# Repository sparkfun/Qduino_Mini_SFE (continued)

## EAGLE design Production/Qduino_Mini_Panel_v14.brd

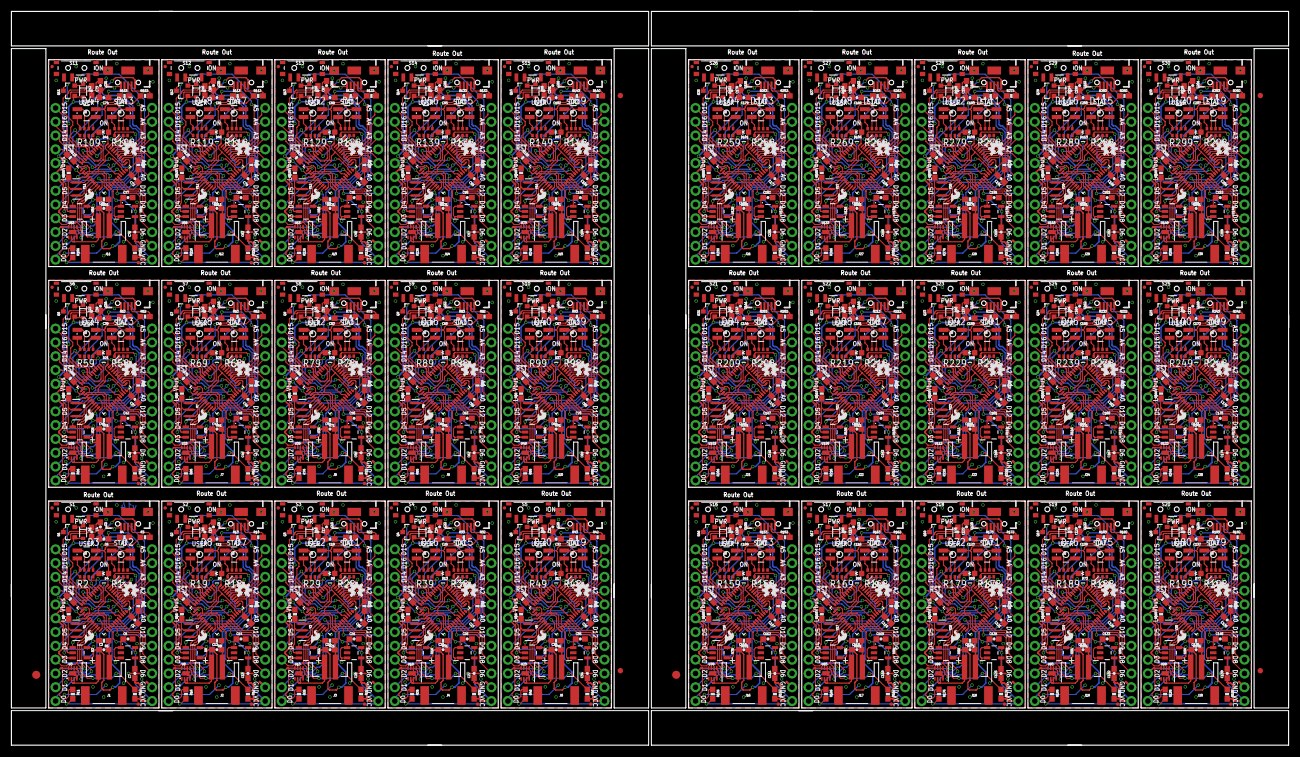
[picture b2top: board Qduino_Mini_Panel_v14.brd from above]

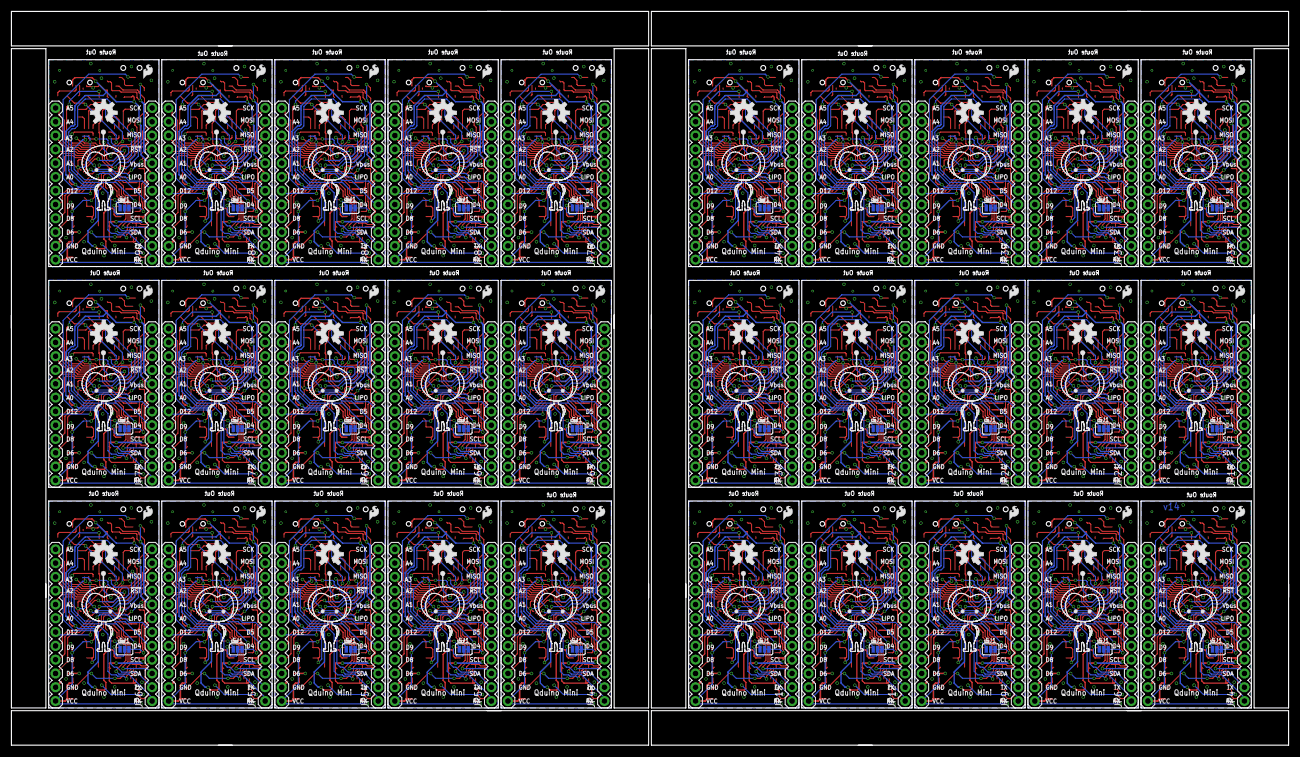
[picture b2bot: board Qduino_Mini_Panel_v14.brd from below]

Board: 2 copper layers, 235.2 x 135.1 mm, 1206 parts (180 on the bottom side), 1530 nets.

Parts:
C1, C2, C8, C9, C15, C16, C22, C23, C29, C30, C36, C37, C43, C44, C50, C51, C57, C58, C64, C65, C71, C72, C78, C79, C85, C86, C92, C93, C99, C100, C106, C107, C113, C114, C120, C121, C127, C128, C134, C135, C141, C142, C148, C149, C155, C156, C162, C163, C169, C170, C176, C177, C183, C184, C190, C191, C197, C198, C204, C205: 4.7uF; 0603-CAP
C3, C4, C5, C10, C12, C14, C17, C19, C21, C24, C26, C28, C31, C33, C35, C38, C40, C42, C45, C47, C49, C52, C54, C56, C59, C61, C63, C66, C68, C70, C73, C75, C77, C80, C82, C84, C87, C89, C91, C94, C96, C98, C101, C103, C105, C108, C110, C112, C115, C117, C119, C122, C124, C126, C129, C131, C133, C136, C138, C140, C143, C145, C147, C150, C152, C154, C157, C159, C161, C164, C166, C168, C171, C173, C175, C178, C180, C182, C185, C187, C189, C192, C194, C196, C199, C201, C203, C206, C208, C210: 1uF; 0603-CAP
C6, C11, C18, C25, C32, C39, C46, C53, C60, C67, C74, C81, C88, C95, C102, C109, C116, C123, C130, C137, C144, C151, C158, C165, C172, C179, C186, C193, C200, C207: 0.1uF; 0603-CAP
C7, C13, C20, C27, C34, C41, C48, C55, C62, C69, C76, C83, C90, C97, C104, C111, C118, C125, C132, C139, C146, C153, C160, C167, C174, C181, C188, C195, C202, C209: 2.2uF; 0603-CAP
D1, D6, D10, D14, D18, D22, D26, D30, D34, D38, D42, D46, D50, D54, D58, D62, D66, D70, D74, D78, D82, D86, D90, D94, D98, D102, D106, D110, D114, D118: BAT20J; SOD-323
D2, D3, D7, D8, D11, D12, D15, D16, D19, D20, D23, D24, D27, D28, D31, D32, D35, D36, D39, D40, D43, D44, D47, D48, D51, D52, D55, D56, D59, D60, D63, D64, D67, D68, D71, D72, D75, D76, D79, D80, D83, D84, D87, D88, D91, D92, D95, D96, D99, D100, D103, D104, D107, D108, D111, D112, D115, D116, D119, D120: P-LCC-4-3
D4, D5, D9, D13, D17, D21, D25, D29, D33, D37, D41, D45, D49, D53, D57, D61, D65, D69, D73, D77, D81, D85, D89, D93, D97, D101, D105, D109, D113, D117: GREEN; LED-0603
E$1, E$4: FIDUCIAL-1.5X3
E$2, E$3, E$5, E$6: FIDUCIAL-1X2
FID1, FID2, FID3, FID4, FID5, FID6, FID7, FID8, FID9, FID10, FID11, FID12, FID13, FID14, FID15, FID16, FID17, FID18, FID19, FID20, FID21, FID22, FID23, FID24, FID25, FID26, FID27, FID28, FID29, FID30, FID31, FID32, FID33, FID34, FID35, FID36, FID37, FID38, FID39, FID40, FID41, FID42, FID43, FID44, FID45, FID46, FID47, FID48, FID49, FID50, FID51, FID52, FID53, FID54, FID55, FID56, FID57, FID58, FID59, FID60: FIDUCIALUFIDUCIAL; MICRO-FIDUCIAL
J1, J2, J3, J4, J5, J6, J7, J8, J9, J10, J11, J12, J13, J14, J15, J16, J17, J18, J19, J20, J21, J22, J23, J24, J25, J26, J27, J28, J29, J30: LiPo; JST-2-SMD
JP1, JP2, JP7, JP10, JP13, JP16, JP19, JP22, JP25, JP28, JP31, JP34, JP37, JP40, JP43, JP46, JP49, JP52, JP55, JP58, JP61, JP64, JP67, JP70, JP73, JP76, JP79, JP82, JP85, JP88: USB-B-MICRO-SMD_V03
JP3, JP4, JP5, JP6, JP8, JP9, JP11, JP12, JP14, JP15, JP17, JP18, JP20, JP21, JP23, JP24, JP26, JP27, JP29, JP30, JP32, JP33, JP35, JP36, JP38, JP39, JP41, JP42, JP44, JP45, JP47, JP48, JP50, JP51, JP53, JP54, JP56, JP57, JP59, JP60, JP62, JP63, JP65, JP66, JP68, JP69, JP71, JP72, JP74, JP75, JP77, JP78, JP80, JP81, JP83, JP84, JP86, JP87, JP89, JP90: 1X12
LOGO1, LOGO4, LOGO7, LOGO10, LOGO13, LOGO16, LOGO19, LOGO22, LOGO25, LOGO28, LOGO31, LOGO34, LOGO37, LOGO40, LOGO43, LOGO46, LOGO49, LOGO52, LOGO55, LOGO58, LOGO61, LOGO64, LOGO67, LOGO70, LOGO73, LOGO76, LOGO79, LOGO82, LOGO85, LOGO88: OSHW-LOGOS; OSHW-LOGO-S
LOGO2, LOGO5, LOGO8, LOGO11, LOGO14, LOGO17, LOGO20, LOGO23, LOGO26, LOGO29, LOGO32, LOGO35, LOGO38, LOGO41, LOGO44, LOGO47, LOGO50, LOGO53, LOGO56, LOGO59, LOGO62, LOGO65, LOGO68, LOGO71, LOGO74, LOGO77, LOGO80, LOGO83, LOGO86, LOGO89: SFE_LOGO_FLAME.1_INCH; SFE_LOGO_FLAME_.1
LOGO3, LOGO6, LOGO9, LOGO12, LOGO15, LOGO18, LOGO21, LOGO24, LOGO27, LOGO30, LOGO33, LOGO36, LOGO39, LOGO42, LOGO45, LOGO48, LOGO51, LOGO54, LOGO57, LOGO60, LOGO63, LOGO66, LOGO69, LOGO72, LOGO75, LOGO78, LOGO81, LOGO84, LOGO87, LOGO90: SFE_LOGO_FLAME.1_INCH; SFE_LOGO_FLAME_.1@1
Q1, Q2, Q3, Q4, Q5, Q6, Q7, Q8, Q9, Q10, Q11, Q12, Q13, Q14, Q15, Q16, Q17, Q18, Q19, Q20, Q21, Q22, Q23, Q24, Q25, Q26, Q27, Q28, Q29, Q30: ZXMP6A13FTA; SOT23-3
R1, R2, R18, R19, R28, R29, R38, R39, R48, R49, R58, R59, R68, R69, R78, R79, R88, R89, R98, R99, R108, R109, R118, R119, R128, R129, R138, R139, R148, R149, R158, R159, R168, R169, R178, R179, R188, R189, R198, R199, R208, R209, R218, R219, R228, R229, R238, R239, R248, R249, R258, R259, R268, R269, R278, R279, R288, R289, R298, R299: 1KΩ; 0603-ARV
R3, R4, R10, R13, R22, R23, R32, R33, R42, R43, R52, R53, R62, R63, R72, R73, R82, R83, R92, R93, R102, R103, R112, R113, R122, R123, R132, R133, R142, R143, R152, R153, R162, R163, R172, R173, R182, R183, R192, R193, R202, R203, R212, R213, R222, R223, R232, R233, R242, R243, R252, R253, R262, R263, R272, R273, R282, R283, R292, R293: 22; 0603-RES
R5, R9, R21, R31, R41, R51, R61, R71, R81, R91, R101, R111, R121, R131, R141, R151, R161, R171, R181, R191, R201, R211, R221, R231, R241, R251, R261, R271, R281, R291: 2.0k; 0603-RES
R6, R14, R24, R34, R44, R54, R64, R74, R84, R94, R104, R114, R124, R134, R144, R154, R164, R174, R184, R194, R204, R214, R224, R234, R244, R254, R264, R274, R284, R294: 100k; 0603-RES
R7, R8, R15, R20, R25, R30, R35, R40, R45, R50, R55, R60, R65, R70, R75, R80, R85, R90, R95, R100, R105, R110, R115, R120, R125, R130, R135, R140, R145, R150, R155, R160, R165, R170, R175, R180, R185, R190, R195, R200, R205, R210, R215, R220, R225, R230, R235, R240, R245, R250, R255, R260, R265, R270, R275, R280, R285, R290, R295, R300: 10K; 0603-RES
R11, R12, R16, R17, R26, R27, R36, R37, R46, R47, R56, R57, R66, R67, R76, R77, R86, R87, R96, R97, R106, R107, R116, R117, R126, R127, R136, R137, R146, R147, R156, R157, R166, R167, R176, R177, R186, R187, R196, R197, R206, R207, R216, R217, R226, R227, R236, R237, R246, R247, R256, R257, R266, R267, R276, R277, R286, R287, R296, R297: 4.7K; 0603-RES
S1, S2, S3, S4, S5, S6, S7, S8, S9, S10, S11, S12, S13, S14, S15, S16, S17, S18, S19, S20, S21, S22, S23, S24, S25, S26, S27, S28, S29, S30: POWER; SWITCH-SPST-SMD-A
SJ1, SJ2, SJ3, SJ4, SJ5, SJ6, SJ7, SJ8, SJ9, SJ10, SJ11, SJ12, SJ13, SJ14, SJ15, SJ16, SJ17, SJ18, SJ19, SJ20, SJ21, SJ22, SJ23, SJ24, SJ25, SJ26, SJ27, SJ28, SJ29, SJ30: PAD-JUMPER-3-2OF3_NC_BY_TRACE_YES_SILK_FULL_BOX
U1, U7, U12, U17, U22, U27, U32, U37, U42, U47, U52, U57, U62, U67, U72, U77, U82, U87, U92, U97, U102, U107, U112, U117, U122, U127, U132, U137, U142, U147: ATMEGA32U41:1-LESS_PASTE; QFN-44-NOPAD_1:1-LESS_PASTE
U2, U6, U11, U16, U21, U26, U31, U36, U41, U46, U51, U56, U61, U66, U71, U76, U81, U86, U91, U96, U101, U106, U111, U116, U121, U126, U131, U136, U141, U146: MCP73831; SOT23-5
U3, U8, U13, U18, U23, U28, U33, U38, U43, U48, U53, U58, U63, U68, U73, U78, U83, U88, U93, U98, U103, U108, U113, U118, U123, U128, U133, U138, U143, U148: MAX17048; DFN-8
U4, U9, U14, U19, U24, U29, U34, U39, U44, U49, U54, U59, U64, U69, U74, U79, U84, U89, U94, U99, U104, U109, U114, U119, U124, U129, U134, U139, U144, U149: AP2112K-3.3TRG-1; SOT23-5
U5, U10, U15, U20, U25, U30, U35, U40, U45, U50, U55, U60, U65, U70, U75, U80, U85, U90, U95, U100, U105, U110, U115, U120, U125, U130, U135, U140, U145, U150: MIGHTYQ-L-SILK; LOGO-LARGE-SILK
U$1, U$2, U$3, U$4, U$5, U$6, U$7, U$8, U$9, U$10, U$11, U$12, U$13, U$14, U$15, U$16, U$17, U$18, U$19, U$20, U$21, U$22, U$23, U$24, U$25, U$26, U$27, U$28, U$29, U$30: OSHW-LOGO-M@1
Y1, Y2, Y3, Y4, Y5, Y6, Y7, Y8, Y9, Y10, Y11, Y12, Y13, Y14, Y15, Y16, Y17, Y18, Y19, Y20, Y21, Y22, Y23, Y24, Y25, Y26, Y27, Y28, Y29, Y30: 8MHZ; RESONATOR-SMD

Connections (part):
!ALRT: U1.1, U3.P$5
!ALRT1: U7.1, U8.P$5
!ALRT2: U12.1, U13.P$5
!ALRT3: U17.1, U18.P$5
!ALRT4: U22.1, U23.P$5
!ALRT5: U27.1, U28.P$5
!ALRT6: U32.1, U33.P$5
!ALRT7: U37.1, U38.P$5
!ALRT8: U42.1, U43.P$5
!ALRT9: U47.1, U48.P$5
!ALRT10: U52.1, U53.P$5
!ALRT11: U57.1, U58.P$5
!ALRT12: U62.1, U63.P$5
!ALRT13: U67.1, U68.P$5
!ALRT14: U72.1, U73.P$5
!ALRT15: U77.1, U78.P$5
!ALRT16: U82.1, U83.P$5
!ALRT17: U87.1, U88.P$5
!ALRT18: U92.1, U93.P$5
!ALRT19: U97.1, U98.P$5
!ALRT20: U102.1, U103.P$5
!ALRT21: U107.1, U108.P$5
!ALRT22: U112.1, U113.P$5
!ALRT23: U117.1, U118.P$5
!ALRT24: U122.1, U123.P$5
!ALRT25: U127.1, U128.P$5
!ALRT26: U132.1, U133.P$5
!ALRT27: U137.1, U138.P$5
!ALRT28: U142.1, U143.P$5
!ALRT29: U147.1, U148.P$5
!RST: JP4.9, R8.1, U1.13
!RST1: JP6.9, R20.1, U7.13
!RST2: JP9.9, R30.1, U12.13
!RST3: JP12.9, R40.1, U17.13
!RST4: JP15.9, R50.1, U22.13
!RST5: JP18.9, R60.1, U27.13
!RST6: JP21.9, R70.1, U32.13
!RST7: JP24.9, R80.1, U37.13
!RST8: JP27.9, R90.1, U42.13
!RST9: JP30.9, R100.1, U47.13
!RST10: JP33.9, R110.1, U52.13
!RST11: JP36.9, R120.1, U57.13
!RST12: JP39.9, R130.1, U62.13
!RST13: JP42.9, R140.1, U67.13
!RST14: JP45.9, R150.1, U72.13
!RST15: JP48.9, R160.1, U77.13
!RST16: JP51.9, R170.1, U82.13
!RST17: JP54.9, R180.1, U87.13
!RST18: JP57.9, R190.1, U92.13
!RST19: JP60.9, R200.1, U97.13
!RST20: JP63.9, R210.1, U102.13
!RST21: JP66.9, R220.1, U107.13
!RST22: JP69.9, R230.1, U112.13
!RST23: JP72.9, R240.1, U117.13
!RST24: JP75.9, R250.1, U122.13
!RST25: JP78.9, R260.1, U127.13
!RST26: JP81.9, R270.1, U132.13
!RST27: JP84.9, R280.1, U137.13
!RST28: JP87.9, R290.1, U142.13
!RST29: JP90.9, R300.1, U147.13
A0: JP3.7, U1.36
A1: JP3.8, U1.37
A2: JP3.9, U1.38
A3: JP3.10, U1.39
A4: JP3.11, U1.40
A5: JP3.12, U1.41
A6: JP5.7, U7.36
A7: JP5.8, U7.37
A8: JP5.9, U7.38
A9: JP5.10, U7.39
A10: JP5.11, U7.40
A11: JP5.12, U7.41
A12: JP8.7, U12.36
A13: JP8.8, U12.37
A14: JP8.9, U12.38
A15: JP8.10, U12.39
A16: JP8.11, U12.40
A17: JP8.12, U12.41
A18: JP11.7, U17.36
A19: JP11.8, U17.37
A20: JP11.9, U17.38
A21: JP11.10, U17.39
A22: JP11.11, U17.40
A23: JP11.12, U17.41
A24: JP14.7, U22.36
A25: JP14.8, U22.37
A26: JP14.9, U22.38
A27: JP14.10, U22.39
A28: JP14.11, U22.40
A29: JP14.12, U22.41
A30: JP17.7, U27.36
A31: JP17.8, U27.37
A32: JP17.9, U27.38
A33: JP17.10, U27.39
A34: JP17.11, U27.40
A35: JP17.12, U27.41
A36: JP20.7, U32.36
A37: JP20.8, U32.37
A38: JP20.9, U32.38
A39: JP20.10, U32.39
A40: JP20.11, U32.40
A41: JP20.12, U32.41
A42: JP23.7, U37.36
A43: JP23.8, U37.37
A44: JP23.9, U37.38
A45: JP23.10, U37.39
A46: JP23.11, U37.40
A47: JP23.12, U37.41
A48: JP26.7, U42.36
A49: JP26.8, U42.37
A50: JP26.9, U42.38
A51: JP26.10, U42.39
A52: JP26.11, U42.40
A53: JP26.12, U42.41
A54: JP29.7, U47.36
A55: JP29.8, U47.37
A56: JP29.9, U47.38
A57: JP29.10, U47.39
A58: JP29.11, U47.40
A59: JP29.12, U47.41
A60: JP32.7, U52.36
A61: JP32.8, U52.37
A62: JP32.9, U52.38
A63: JP32.10, U52.39
A64: JP32.11, U52.40
A65: JP32.12, U52.41
A66: JP35.7, U57.36
A67: JP35.8, U57.37
A68: JP35.9, U57.38
A69: JP35.10, U57.39
A70: JP35.11, U57.40
A71: JP35.12, U57.41
A72: JP38.7, U62.36
A73: JP38.8, U62.37
A74: JP38.9, U62.38
A75: JP38.10, U62.39
A76: JP38.11, U62.40
A77: JP38.12, U62.41
A78: JP41.7, U67.36
A79: JP41.8, U67.37
A80: JP41.9, U67.38
A81: JP41.10, U67.39
A82: JP41.11, U67.40
A83: JP41.12, U67.41
A84: JP44.7, U72.36
A85: JP44.8, U72.37
A86: JP44.9, U72.38
A87: JP44.10, U72.39
A88: JP44.11, U72.40
A89: JP44.12, U72.41
A90: JP47.7, U77.36
A91: JP47.8, U77.37
A92: JP47.9, U77.38
A93: JP47.10, U77.39
A94: JP47.11, U77.40
A95: JP47.12, U77.41
A96: JP50.7, U82.36
A97: JP50.8, U82.37
A98: JP50.9, U82.38
A99: JP50.10, U82.39
A100: JP50.11, U82.40
A101: JP50.12, U82.41
A102: JP53.7, U87.36
A103: JP53.8, U87.37
A104: JP53.9, U87.38
A105: JP53.10, U87.39
A106: JP53.11, U87.40
A107: JP53.12, U87.41
A108: JP56.7, U92.36
A109: JP56.8, U92.37
A110: JP56.9, U92.38
A111: JP56.10, U92.39
A112: JP56.11, U92.40
A113: JP56.12, U92.41
A114: JP59.7, U97.36
A115: JP59.8, U97.37
A116: JP59.9, U97.38
A117: JP59.10, U97.39
A118: JP59.11, U97.40
A119: JP59.12, U97.41
A120: JP62.7, U102.36
A121: JP62.8, U102.37
A122: JP62.9, U102.38
A123: JP62.10, U102.39
A124: JP62.11, U102.40
A125: JP62.12, U102.41
A126: JP65.7, U107.36
A127: JP65.8, U107.37
A128: JP65.9, U107.38
A129: JP65.10, U107.39
A130: JP65.11, U107.40
A131: JP65.12, U107.41
A132: JP68.7, U112.36
A133: JP68.8, U112.37
A134: JP68.9, U112.38
A135: JP68.10, U112.39
A136: JP68.11, U112.40
A137: JP68.12, U112.41
A138: JP71.7, U117.36
A139: JP71.8, U117.37
A140: JP71.9, U117.38
A141: JP71.10, U117.39
A142: JP71.11, U117.40
A143: JP71.12, U117.41
A144: JP74.7, U122.36
A145: JP74.8, U122.37
A146: JP74.9, U122.38
A147: JP74.10, U122.39
A148: JP74.11, U122.40
A149: JP74.12, U122.41
A150: JP77.7, U127.36
A151: JP77.8, U127.37
A152: JP77.9, U127.38
A153: JP77.10, U127.39
A154: JP77.11, U127.40
A155: JP77.12, U127.41
A156: JP80.7, U132.36
A157: JP80.8, U132.37
A158: JP80.9, U132.38
A159: JP80.10, U132.39
A160: JP80.11, U132.40
A161: JP80.12, U132.41
A162: JP83.7, U137.36
A163: JP83.8, U137.37
A164: JP83.9, U137.38
A165: JP83.10, U137.39
A166: JP83.11, U137.40
A167: JP83.12, U137.41
A168: JP86.7, U142.36
A169: JP86.8, U142.37
A170: JP86.9, U142.38
A171: JP86.10, U142.39
A172: JP86.11, U142.40
A173: JP86.12, U142.41
A174: JP89.7, U147.36
A175: JP89.8, U147.37
A176: JP89.9, U147.38
A177: JP89.10, U147.39
A178: JP89.11, U147.40
A179: JP89.12, U147.41
AREF: C6.1, U1.42
AREF1: C11.1, U7.42
AREF2: C18.1, U12.42
AREF3: C25.1, U17.42
AREF4: C32.1, U22.42
AREF5: C39.1, U27.42
AREF6: C46.1, U32.42
AREF7: C53.1, U37.42
AREF8: C60.1, U42.42
AREF9: C67.1, U47.42
AREF10: C74.1, U52.42
AREF11: C81.1, U57.42
AREF12: C88.1, U62.42
AREF13: C95.1, U67.42
AREF14: C102.1, U72.42
AREF15: C109.1, U77.42
AREF16: C116.1, U82.42
AREF17: C123.1, U87.42
AREF18: C130.1, U92.42
AREF19: C137.1, U97.42
AREF20: C144.1, U102.42
AREF21: C151.1, U107.42
AREF22: C158.1, U112.42
AREF23: C165.1, U117.42
AREF24: C172.1, U122.42
AREF25: C179.1, U127.42
AREF26: C186.1, U132.42
AREF27: C193.1, U137.42
AREF28: C200.1, U142.42
AREF29: C207.1, U147.42
D1: JP6.5, U7.25
D2: JP6.6, U7.31
D3: JP5.4, U7.28
D4: JP4.5, U1.25
D5: JP4.6, U1.31
D6: JP3.3, U1.27
D7: JP5.5, U7.29
D8: JP3.4, U1.28
D9: JP3.5, U1.29
D10: R2.2, U1.30
D11: R2.1, U1.12
D12: JP3.6, U1.26
D13: R2.3, U1.32
D14: R19.2, U7.30
D15: R19.1, U7.12
D16: JP5.6, U7.26
D17: R19.3, U7.32
D18: JP5.3, U7.27
D19: JP9.5, U12.25
D20: JP9.6, U12.31
D21: JP8.4, U12.28
D22: JP8.5, U12.29
D23: R29.2, U12.30
D24: R29.1, U12.12
D25: JP8.6, U12.26
D26: R29.3, U12.32
D27: JP8.3, U12.27
D28: JP12.5, U17.25
D29: JP12.6, U17.31
D30: JP11.4, U17.28
D31: JP11.5, U17.29
D32: R39.2, U17.30
D33: R39.1, U17.12
D34: JP11.6, U17.26
D35: R39.3, U17.32
D36: JP11.3, U17.27
D37: JP15.5, U22.25
D38: JP15.6, U22.31
D39: JP14.4, U22.28
D40: JP14.5, U22.29
D41: R49.2, U22.30
D42: R49.1, U22.12
D43: JP14.6, U22.26
D44: R49.3, U22.32
D45: JP14.3, U22.27
D46: JP18.5, U27.25
D47: JP18.6, U27.31
D48: JP17.4, U27.28
D49: JP17.5, U27.29
D50: R59.2, U27.30
D51: R59.1, U27.12
D52: JP17.6, U27.26
D53: R59.3, U27.32
D54: JP17.3, U27.27
D55: JP21.5, U32.25
D56: JP21.6, U32.31
D57: JP20.4, U32.28
D58: JP20.5, U32.29
D59: R69.2, U32.30
D60: R69.1, U32.12
D61: JP20.6, U32.26
D62: R69.3, U32.32
D63: JP20.3, U32.27
D64: JP24.5, U37.25
D65: JP24.6, U37.31
D66: JP23.4, U37.28
D67: JP23.5, U37.29
D68: R79.2, U37.30
D69: R79.1, U37.12
D70: JP23.6, U37.26
D71: R79.3, U37.32
D72: JP23.3, U37.27
D73: JP27.5, U42.25
D74: JP27.6, U42.31
D75: JP26.4, U42.28
D76: JP26.5, U42.29
D77: R89.2, U42.30
D78: R89.1, U42.12
D79: JP26.6, U42.26
D80: R89.3, U42.32
D81: JP26.3, U42.27
D82: JP30.5, U47.25
D83: JP30.6, U47.31
D84: JP29.4, U47.28
D85: JP29.5, U47.29
D86: R99.2, U47.30
D87: R99.1, U47.12
D88: JP29.6, U47.26
D89: R99.3, U47.32
D90: JP29.3, U47.27
D91: JP33.5, U52.25
D92: JP33.6, U52.31
D93: JP32.4, U52.28
D94: JP32.5, U52.29
D95: R109.2, U52.30
D96: R109.1, U52.12
D97: JP32.6, U52.26
D98: R109.3, U52.32
D99: JP32.3, U52.27
D100: JP36.5, U57.25
D101: JP36.6, U57.31
D102: JP35.4, U57.28
D103: JP35.5, U57.29
D104: R119.2, U57.30
D105: R119.1, U57.12
D106: JP35.6, U57.26
D107: R119.3, U57.32
D108: JP35.3, U57.27
D109: JP39.5, U62.25
D110: JP39.6, U62.31
D111: JP38.4, U62.28
D112: JP38.5, U62.29
D113: R129.2, U62.30
D114: R129.1, U62.12
D115: JP38.6, U62.26
D116: R129.3, U62.32
D117: JP38.3, U62.27
D118: JP42.5, U67.25
D119: JP42.6, U67.31
D120: JP41.4, U67.28
D121: JP41.5, U67.29
D122: R139.2, U67.30
D123: R139.1, U67.12
D124: JP41.6, U67.26
D125: R139.3, U67.32
D126: JP41.3, U67.27
D127: JP45.5, U72.25
D128: JP45.6, U72.31
D129: JP44.4, U72.28
D130: JP44.5, U72.29
D131: R149.2, U72.30
D132: R149.1, U72.12
D133: JP44.6, U72.26
D134: R149.3, U72.32
D135: JP44.3, U72.27
D136: JP48.5, U77.25
D137: JP48.6, U77.31
D138: JP47.4, U77.28
D139: JP47.5, U77.29
D140: R159.2, U77.30
D141: R159.1, U77.12
D142: JP47.6, U77.26
D143: R159.3, U77.32
D144: JP47.3, U77.27
D145: JP51.5, U82.25
D146: JP51.6, U82.31
D147: JP50.4, U82.28
D148: JP50.5, U82.29
D149: R169.2, U82.30
D150: R169.1, U82.12
D151: JP50.6, U82.26
D152: R169.3, U82.32
D153: JP50.3, U82.27
D154: JP54.5, U87.25
D155: JP54.6, U87.31
D156: JP53.4, U87.28
D157: JP53.5, U87.29
D158: R179.2, U87.30
D159: R179.1, U87.12
D160: JP53.6, U87.26
D161: R179.3, U87.32
D162: JP53.3, U87.27
D163: JP57.5, U92.25
D164: JP57.6, U92.31
D165: JP56.4, U92.28
D166: JP56.5, U92.29
D167: R189.2, U92.30
D168: R189.1, U92.12
D169: JP56.6, U92.26
D170: R189.3, U92.32
D171: JP56.3, U92.27
D172: JP60.5, U97.25
D173: JP60.6, U97.31
D174: JP59.4, U97.28
D175: JP59.5, U97.29
D176: R199.2, U97.30
D177: R199.1, U97.12
D178: JP59.6, U97.26
D179: R199.3, U97.32
D180: JP59.3, U97.27
D181: JP63.5, U102.25
D182: JP63.6, U102.31
D183: JP62.4, U102.28
D184: JP62.5, U102.29
D185: R209.2, U102.30
D186: R209.1, U102.12
D187: JP62.6, U102.26
D188: R209.3, U102.32
D189: JP62.3, U102.27
D190: JP66.5, U107.25
D191: JP66.6, U107.31
D192: JP65.4, U107.28
D193: JP65.5, U107.29
D194: R219.2, U107.30
D195: R219.1, U107.12
D196: JP65.6, U107.26
D197: R219.3, U107.32
D198: JP65.3, U107.27
D199: JP69.5, U112.25
D200: JP69.6, U112.31
D201: JP68.4, U112.28
D202: JP68.5, U112.29
D203: R229.2, U112.30
D204: R229.1, U112.12
D205: JP68.6, U112.26
D206: R229.3, U112.32
D207: JP68.3, U112.27
D208: JP72.5, U117.25
D209: JP72.6, U117.31
D210: JP71.4, U117.28
D211: JP71.5, U117.29
D212: R239.2, U117.30
D213: R239.1, U117.12
D214: JP71.6, U117.26
D215: R239.3, U117.32
D216: JP71.3, U117.27
D217: JP75.5, U122.25
D218: JP75.6, U122.31
D219: JP74.4, U122.28
D220: JP74.5, U122.29
D221: R249.2, U122.30
D222: R249.1, U122.12
D223: JP74.6, U122.26
D224: R249.3, U122.32
D225: JP74.3, U122.27
D226: JP78.5, U127.25
D227: JP78.6, U127.31
D228: JP77.4, U127.28
D229: JP77.5, U127.29
D230: R259.2, U127.30
D231: R259.1, U127.12
D232: JP77.6, U127.26
D233: R259.3, U127.32
D234: JP77.3, U127.27
D235: JP81.5, U132.25
D236: JP81.6, U132.31
D237: JP80.4, U132.28
D238: JP80.5, U132.29
D239: R269.2, U132.30
D240: R269.1, U132.12
D241: JP80.6, U132.26
D242: R269.3, U132.32
D243: JP80.3, U132.27
D244: JP84.5, U137.25
D245: JP84.6, U137.31
D246: JP83.4, U137.28
D247: JP83.5, U137.29
D248: R279.2, U137.30
D249: R279.1, U137.12
D250: JP83.6, U137.26
D251: R279.3, U137.32
D252: JP83.3, U137.27
D253: JP87.5, U142.25
D254: JP87.6, U142.31
D255: JP86.4, U142.28
D256: JP86.5, U142.29
D257: R289.2, U142.30
D258: R289.1, U142.12
D259: JP86.6, U142.26
D260: R289.3, U142.32
D261: JP86.3, U142.27
D262: JP90.5, U147.25
D263: JP90.6, U147.31
D264: JP89.4, U147.28
D265: JP89.5, U147.29
D266: R299.2, U147.30
D267: R299.1, U147.12
D268: JP89.6, U147.26
D269: R299.3, U147.32
D270: JP89.3, U147.27
D+: R4.1, U1.4
D+1: R13.1, U7.4
D+2: R23.1, U12.4
D+3: R33.1, U17.4
D+4: R43.1, U22.4
D+5: R53.1, U27.4
D+6: R63.1, U32.4
D+7: R73.1, U37.4
D+8: R83.1, U42.4
D+9: R93.1, U47.4
D+10: R103.1, U52.4
D+11: R113.1, U57.4
D+12: R123.1, U62.4
D+13: R133.1, U67.4
D+14: R143.1, U72.4
D+15: R153.1, U77.4
D+16: R163.1, U82.4
D+17: R173.1, U87.4
D+18: R183.1, U92.4
D+19: R193.1, U97.4
D+20: R203.1, U102.4
D+21: R213.1, U107.4
D+22: R223.1, U112.4
D+23: R233.1, U117.4
D+24: R243.1, U122.4
D+25: R253.1, U127.4
D+26: R263.1, U132.4
D+27: R273.1, U137.4
D+28: R283.1, U142.4
D+29: R293.1, U147.4
D-: R3.1, U1.3
D-1: R10.1, U7.3
D-2: R22.1, U12.3
D-3: R32.1, U17.3
D-4: R42.1, U22.3
D-5: R52.1, U27.3
D-6: R62.1, U32.3
D-7: R72.1, U37.3
D-8: R82.1, U42.3
D-9: R92.1, U47.3
D-10: R102.1, U52.3
D-11: R112.1, U57.3
D-12: R122.1, U62.3
D-13: R132.1, U67.3
D-14: R142.1, U72.3
D-15: R152.1, U77.3
D-16: R162.1, U82.3
D-17: R172.1, U87.3
D-18: R182.1, U92.3
D-19: R192.1, U97.3
D-20: R202.1, U102.3
D-21: R212.1, U107.3
D-22: R222.1, U112.3
D-23: R232.1, U117.3
D-24: R242.1, U122.3
D-25: R252.1, U127.3
D-26: R262.1, U132.3
D-27: R272.1, U137.3
D-28: R282.1, U142.3
D-29: R292.1, U147.3
GND: C1.2, C2.2, C3.2, C4.2, C5.2, C6.2, C7.2, J1.1, JP2.GND1, JP3.2, R2.5, R5.1, R6.1, R7.1, U1.5, U1.15, U1.23, U1.33, U1.35, U1.43, U2.2, U3.P$1, U3.P$4, U3.P$6, U3.P$9, U4.2, U4.4, Y1.2
GND1: C8.2, C9.2, C10.2, C11.2, C12.2, C13.2, C14.2, J2.1, JP1.GND1, JP5.2, R9.1, R14.1, R15.1, R19.5, U6.2, U7.5, U7.15, U7.23, U7.33, U7.35, U7.43, U8.P$1, U8.P$4, U8.P$6, U8.P$9, U9.2, U9.4, Y2.2
GND2: C15.2, C16.2, C17.2, C18.2, C19.2, C20.2, C21.2, J3.1, JP7.GND1, JP8.2, R21.1, R24.1, R25.1, R29.5, U11.2, U12.5, U12.15, U12.23, U12.33, U12.35, U12.43, U13.P$1, U13.P$4, U13.P$6, U13.P$9, U14.2, U14.4, Y3.2
GND3: C22.2, C23.2, C24.2, C25.2, C26.2, C27.2, C28.2, J4.1, JP10.GND1, JP11.2, R31.1, R34.1, R35.1, R39.5, U16.2, U17.5, U17.15, U17.23, U17.33, U17.35, U17.43, U18.P$1, U18.P$4, U18.P$6, U18.P$9, U19.2, U19.4, Y4.2
GND4: C29.2, C30.2, C31.2, C32.2, C33.2, C34.2, C35.2, J5.1, JP13.GND1, JP14.2, R41.1, R44.1, R45.1, R49.5, U21.2, U22.5, U22.15, U22.23, U22.33, U22.35, U22.43, U23.P$1, U23.P$4, U23.P$6, U23.P$9, U24.2, U24.4, Y5.2
GND5: C36.2, C37.2, C38.2, C39.2, C40.2, C41.2, C42.2, J6.1, JP16.GND1, JP17.2, R51.1, R54.1, R55.1, R59.5, U26.2, U27.5, U27.15, U27.23, U27.33, U27.35, U27.43, U28.P$1, U28.P$4, U28.P$6, U28.P$9, U29.2, U29.4, Y6.2
GND6: C43.2, C44.2, C45.2, C46.2, C47.2, C48.2, C49.2, J7.1, JP19.GND1, JP20.2, R61.1, R64.1, R65.1, R69.5, U31.2, U32.5, U32.15, U32.23, U32.33, U32.35, U32.43, U33.P$1, U33.P$4, U33.P$6, U33.P$9, U34.2, U34.4, Y7.2
GND7: C50.2, C51.2, C52.2, C53.2, C54.2, C55.2, C56.2, J8.1, JP22.GND1, JP23.2, R71.1, R74.1, R75.1, R79.5, U36.2, U37.5, U37.15, U37.23, U37.33, U37.35, U37.43, U38.P$1, U38.P$4, U38.P$6, U38.P$9, U39.2, U39.4, Y8.2
GND8: C57.2, C58.2, C59.2, C60.2, C61.2, C62.2, C63.2, J9.1, JP25.GND1, JP26.2, R81.1, R84.1, R85.1, R89.5, U41.2, U42.5, U42.15, U42.23, U42.33, U42.35, U42.43, U43.P$1, U43.P$4, U43.P$6, U43.P$9, U44.2, U44.4, Y9.2
GND9: C64.2, C65.2, C66.2, C67.2, C68.2, C69.2, C70.2, J10.1, JP28.GND1, JP29.2, R91.1, R94.1, R95.1, R99.5, U46.2, U47.5, U47.15, U47.23, U47.33, U47.35, U47.43, U48.P$1, U48.P$4, U48.P$6, U48.P$9, U49.2, U49.4, Y10.2
GND10: C71.2, C72.2, C73.2, C74.2, C75.2, C76.2, C77.2, J11.1, JP31.GND1, JP32.2, R101.1, R104.1, R105.1, R109.5, U51.2, U52.5, U52.15, U52.23, U52.33, U52.35, U52.43, U53.P$1, U53.P$4, U53.P$6, U53.P$9, U54.2, U54.4, Y11.2
GND11: C78.2, C79.2, C80.2, C81.2, C82.2, C83.2, C84.2, J12.1, JP34.GND1, JP35.2, R111.1, R114.1, R115.1, R119.5, U56.2, U57.5, U57.15, U57.23, U57.33, U57.35, U57.43, U58.P$1, U58.P$4, U58.P$6, U58.P$9, U59.2, U59.4, Y12.2
GND12: C85.2, C86.2, C87.2, C88.2, C89.2, C90.2, C91.2, J13.1, JP37.GND1, JP38.2, R121.1, R124.1, R125.1, R129.5, U61.2, U62.5, U62.15, U62.23, U62.33, U62.35, U62.43, U63.P$1, U63.P$4, U63.P$6, U63.P$9, U64.2, U64.4, Y13.2
GND13: C92.2, C93.2, C94.2, C95.2, C96.2, C97.2, C98.2, J14.1, JP40.GND1, JP41.2, R131.1, R134.1, R135.1, R139.5, U66.2, U67.5, U67.15, U67.23, U67.33, U67.35, U67.43, U68.P$1, U68.P$4, U68.P$6, U68.P$9, U69.2, U69.4, Y14.2
GND14: C99.2, C100.2, C101.2, C102.2, C103.2, C104.2, C105.2, J15.1, JP43.GND1, JP44.2, R141.1, R144.1, R145.1, R149.5, U71.2, U72.5, U72.15, U72.23, U72.33, U72.35, U72.43, U73.P$1, U73.P$4, U73.P$6, U73.P$9, U74.2, U74.4, Y15.2
GND15: C106.2, C107.2, C108.2, C109.2, C110.2, C111.2, C112.2, J16.1, JP46.GND1, JP47.2, R151.1, R154.1, R155.1, R159.5, U76.2, U77.5, U77.15, U77.23, U77.33, U77.35, U77.43, U78.P$1, U78.P$4, U78.P$6, U78.P$9, U79.2, U79.4, Y16.2
GND16: C113.2, C114.2, C115.2, C116.2, C117.2, C118.2, C119.2, J17.1, JP49.GND1, JP50.2, R161.1, R164.1, R165.1, R169.5, U81.2, U82.5, U82.15, U82.23, U82.33, U82.35, U82.43, U83.P$1, U83.P$4, U83.P$6, U83.P$9, U84.2, U84.4, Y17.2
GND17: C120.2, C121.2, C122.2, C123.2, C124.2, C125.2, C126.2, J18.1, JP52.GND1, JP53.2, R171.1, R174.1, R175.1, R179.5, U86.2, U87.5, U87.15, U87.23, U87.33, U87.35, U87.43, U88.P$1, U88.P$4, U88.P$6, U88.P$9, U89.2, U89.4, Y18.2
GND18: C127.2, C128.2, C129.2, C130.2, C131.2, C132.2, C133.2, J19.1, JP55.GND1, JP56.2, R181.1, R184.1, R185.1, R189.5, U91.2, U92.5, U92.15, U92.23, U92.33, U92.35, U92.43, U93.P$1, U93.P$4, U93.P$6, U93.P$9, U94.2, U94.4, Y19.2
GND19: C134.2, C135.2, C136.2, C137.2, C138.2, C139.2, C140.2, J20.1, JP58.GND1, JP59.2, R191.1, R194.1, R195.1, R199.5, U96.2, U97.5, U97.15, U97.23, U97.33, U97.35, U97.43, U98.P$1, U98.P$4, U98.P$6, U98.P$9, U99.2, U99.4, Y20.2
GND20: C141.2, C142.2, C143.2, C144.2, C145.2, C146.2, C147.2, J21.1, JP61.GND1, JP62.2, R201.1, R204.1, R205.1, R209.5, U101.2, U102.5, U102.15, U102.23, U102.33, U102.35, U102.43, U103.P$1, U103.P$4, U103.P$6, U103.P$9, U104.2, U104.4, Y21.2
GND21: C148.2, C149.2, C150.2, C151.2, C152.2, C153.2, C154.2, J22.1, JP64.GND1, JP65.2, R211.1, R214.1, R215.1, R219.5, U106.2, U107.5, U107.15, U107.23, U107.33, U107.35, U107.43, U108.P$1, U108.P$4, U108.P$6, U108.P$9, U109.2, U109.4, Y22.2
GND22: C155.2, C156.2, C157.2, C158.2, C159.2, C160.2, C161.2, J23.1, JP67.GND1, JP68.2, R221.1, R224.1, R225.1, R229.5, U111.2, U112.5, U112.15, U112.23, U112.33, U112.35, U112.43, U113.P$1, U113.P$4, U113.P$6, U113.P$9, U114.2, U114.4, Y23.2
GND23: C162.2, C163.2, C164.2, C165.2, C166.2, C167.2, C168.2, J24.1, JP70.GND1, JP71.2, R231.1, R234.1, R235.1, R239.5, U116.2, U117.5, U117.15, U117.23, U117.33, U117.35, U117.43, U118.P$1, U118.P$4, U118.P$6, U118.P$9, U119.2, U119.4, Y24.2
GND24: C169.2, C170.2, C171.2, C172.2, C173.2, C174.2, C175.2, J25.1, JP73.GND1, JP74.2, R241.1, R244.1, R245.1, R249.5, U121.2, U122.5, U122.15, U122.23, U122.33, U122.35, U122.43, U123.P$1, U123.P$4, U123.P$6, U123.P$9, U124.2, U124.4, Y25.2
GND25: C176.2, C177.2, C178.2, C179.2, C180.2, C181.2, C182.2, J26.1, JP76.GND1, JP77.2, R251.1, R254.1, R255.1, R259.5, U126.2, U127.5, U127.15, U127.23, U127.33, U127.35, U127.43, U128.P$1, U128.P$4, U128.P$6, U128.P$9, U129.2, U129.4, Y26.2
GND26: C183.2, C184.2, C185.2, C186.2, C187.2, C188.2, C189.2, J27.1, JP79.GND1, JP80.2, R261.1, R264.1, R265.1, R269.5, U131.2, U132.5, U132.15, U132.23, U132.33, U132.35, U132.43, U133.P$1, U133.P$4, U133.P$6, U133.P$9, U134.2, U134.4, Y27.2
GND27: C190.2, C191.2, C192.2, C193.2, C194.2, C195.2, C196.2, J28.1, JP82.GND1, JP83.2, R271.1, R274.1, R275.1, R279.5, U136.2, U137.5, U137.15, U137.23, U137.33, U137.35, U137.43, U138.P$1, U138.P$4, U138.P$6, U138.P$9, U139.2, U139.4, Y28.2
GND28: C197.2, C198.2, C199.2, C200.2, C201.2, C202.2, C203.2, J29.1, JP85.GND1, JP86.2, R281.1, R284.1, R285.1, R289.5, U141.2, U142.5, U142.15, U142.23, U142.33, U142.35, U142.43, U143.P$1, U143.P$4, U143.P$6, U143.P$9, U144.2, U144.4, Y29.2
GND29: C204.2, C205.2, C206.2, C207.2, C208.2, C209.2, C210.2, J30.1, JP88.GND1, JP89.2, R291.1, R294.1, R295.1, R299.5, U146.2, U147.5, U147.15, U147.23, U147.33, U147.35, U147.43, U148.P$1, U148.P$4, U148.P$6, U148.P$9, U149.2, U149.4, Y30.2
INMOSFET: D1.C, Q1.2, S1.3
INMOSFET1: D6.C, Q2.2, S2.3
INMOSFET2: D10.C, Q3.2, S3.3
INMOSFET3: D14.C, Q4.2, S4.3
INMOSFET4: D18.C, Q5.2, S5.3
INMOSFET5: D22.C, Q6.2, S6.3
INMOSFET6: D26.C, Q7.2, S7.3
INMOSFET7: D30.C, Q8.2, S8.3
INMOSFET8: D34.C, Q9.2, S9.3
INMOSFET9: D38.C, Q10.2, S10.3
INMOSFET10: D42.C, Q11.2, S11.3
INMOSFET11: D46.C, Q12.2, S12.3
INMOSFET12: D50.C, Q13.2, S13.3
INMOSFET13: D54.C, Q14.2, S14.3
INMOSFET14: D58.C, Q15.2, S15.3
INMOSFET15: D62.C, Q16.2, S16.3
INMOSFET16: D66.C, Q17.2, S17.3
INMOSFET17: D70.C, Q18.2, S18.3
INMOSFET18: D74.C, Q19.2, S19.3
INMOSFET19: D78.C, Q20.2, S20.3
INMOSFET20: D82.C, Q21.2, S21.3
INMOSFET21: D86.C, Q22.2, S22.3
INMOSFET22: D90.C, Q23.2, S23.3
INMOSFET23: D94.C, Q24.2, S24.3
INMOSFET24: D98.C, Q25.2, S25.3
INMOSFET25: D102.C, Q26.2, S26.3
INMOSFET26: D106.C, Q27.2, S27.3
INMOSFET27: D110.C, Q28.2, S28.3
INMOSFET28: D114.C, Q29.2, S29.3
INMOSFET29: D118.C, Q30.2, S30.3
LIPO: C2.1, J1.2, JP4.7, Q1.3, U2.3, U3.P$2, U3.P$3
LIPO2: C8.1, J2.2, JP6.7, Q2.3, U6.3, U8.P$2, U8.P$3
LIPO3: C15.1, J3.2, JP9.7, Q3.3, U11.3, U13.P$2, U13.P$3
LIPO4: C22.1, J4.2, JP12.7, Q4.3, U16.3, U18.P$2, U18.P$3
LIPO5: C29.1, J5.2, JP15.7, Q5.3, U21.3, U23.P$2, U23.P$3
LIPO6: C36.1, J6.2, JP18.7, Q6.3, U26.3, U28.P$2, U28.P$3
LIPO7: C43.1, J7.2, JP21.7, Q7.3, U31.3, U33.P$2, U33.P$3
LIPO8: C50.1, J8.2, JP24.7, Q8.3, U36.3, U38.P$2, U38.P$3
LIPO9: C57.1, J9.2, JP27.7, Q9.3, U41.3, U43.P$2, U43.P$3
LIPO10: C64.1, J10.2, JP30.7, Q10.3, U46.3, U48.P$2, U48.P$3
LIPO11: C71.1, J11.2, JP33.7, Q11.3, U51.3, U53.P$2, U53.P$3
LIPO12: C78.1, J12.2, JP36.7, Q12.3, U56.3, U58.P$2, U58.P$3
LIPO13: C85.1, J13.2, JP39.7, Q13.3, U61.3, U63.P$2, U63.P$3
LIPO14: C92.1, J14.2, JP42.7, Q14.3, U66.3, U68.P$2, U68.P$3
LIPO15: C99.1, J15.2, JP45.7, Q15.3, U71.3, U73.P$2, U73.P$3
LIPO16: C106.1, J16.2, JP48.7, Q16.3, U76.3, U78.P$2, U78.P$3
LIPO17: C113.1, J17.2, JP51.7, Q17.3, U81.3, U83.P$2, U83.P$3
LIPO18: C120.1, J18.2, JP54.7, Q18.3, U86.3, U88.P$2, U88.P$3
LIPO19: C127.1, J19.2, JP57.7, Q19.3, U91.3, U93.P$2, U93.P$3
LIPO20: C134.1, J20.2, JP60.7, Q20.3, U96.3, U98.P$2, U98.P$3
LIPO21: C141.1, J21.2, JP63.7, Q21.3, U101.3, U103.P$2, U103.P$3
LIPO22: C148.1, J22.2, JP66.7, Q22.3, U106.3, U108.P$2, U108.P$3
LIPO23: C155.1, J23.2, JP69.7, Q23.3, U111.3, U113.P$2, U113.P$3
LIPO24: C162.1, J24.2, JP72.7, Q24.3, U116.3, U118.P$2, U118.P$3
LIPO25: C169.1, J25.2, JP75.7, Q25.3, U121.3, U123.P$2, U123.P$3
LIPO26: C176.1, J26.2, JP78.7, Q26.3, U126.3, U128.P$2, U128.P$3
LIPO27: C183.1, J27.2, JP81.7, Q27.3, U131.3, U133.P$2, U133.P$3
LIPO28: C190.1, J28.2, JP84.7, Q28.3, U136.3, U138.P$2, U138.P$3
LIPO29: C197.1, J29.2, JP87.7, Q29.3, U141.3, U143.P$2, U143.P$3
LIPO30: C204.1, J30.2, JP90.7, Q30.3, U146.3, U148.P$2, U148.P$3
MISO: JP4.10, U1.11
MISO2: JP6.10, U7.11
MISO3: JP9.10, U12.11
MISO4: JP12.10, U17.11
MISO5: JP15.10, U22.11
MISO6: JP18.10, U27.11
MISO7: JP21.10, U32.11
MISO8: JP24.10, U37.11
MISO9: JP27.10, U42.11
MISO10: JP30.10, U47.11
MISO11: JP33.10, U52.11
MISO12: JP36.10, U57.11
MISO13: JP39.10, U62.11
MISO14: JP42.10, U67.11
MISO15: JP45.10, U72.11
MISO16: JP48.10, U77.11
MISO17: JP51.10, U82.11
MISO18: JP54.10, U87.11
MISO19: JP57.10, U92.11
MISO20: JP60.10, U97.11
MISO21: JP63.10, U102.11
MISO22: JP66.10, U107.11
MISO23: JP69.10, U112.11
MISO24: JP72.10, U117.11
MISO25: JP75.10, U122.11
MISO26: JP78.10, U127.11
MISO27: JP81.10, U132.11
MISO28: JP84.10, U137.11
MISO29: JP87.10, U142.11
MISO30: JP90.10, U147.11
MOSI: JP4.11, U1.10
MOSI2: JP6.11, U7.10
MOSI3: JP9.11, U12.10
MOSI4: JP12.11, U17.10
MOSI5: JP15.11, U22.10
MOSI6: JP18.11, U27.10
MOSI7: JP21.11, U32.10
MOSI8: JP24.11, U37.10
MOSI9: JP27.11, U42.10
MOSI10: JP30.11, U47.10
MOSI11: JP33.11, U52.10
MOSI12: JP36.11, U57.10
MOSI13: JP39.11, U62.10
MOSI14: JP42.11, U67.10
MOSI15: JP45.11, U72.10
MOSI16: JP48.11, U77.10
MOSI17: JP51.11, U82.10
MOSI18: JP54.11, U87.10
MOSI19: JP57.11, U92.10
MOSI20: JP60.11, U97.10
MOSI21: JP63.11, U102.10
MOSI22: JP66.11, U107.10
MOSI23: JP69.11, U112.10
MOSI24: JP72.11, U117.10
MOSI25: JP75.11, U122.10
MOSI26: JP78.11, U127.10
MOSI27: JP81.11, U132.10
MOSI28: JP84.11, U137.10
MOSI29: JP87.11, U142.10
MOSI30: JP90.11, U147.10
unnamed: D2.3, R1.6
unnamed: D2.2, R1.8
unnamed: D3.3, R2.6
unnamed: D4.C, R2.4
unnamed: R7.2, SJ1.3
unnamed: R5.2, SJ1.1
unnamed: D3.2, R2.8
unnamed: R15.2, SJ2.3
unnamed: R9.2, SJ2.1
unnamed: D7.1, R18.7
unnamed: D8.1, R19.7
unnamed: D5.C, R19.4
unnamed: D8.3, R19.6
unnamed: D8.2, R19.8
unnamed: D7.3, R18.6
unnamed: D7.2, R18.8
unnamed: R25.2, SJ3.3
unnamed: R21.2, SJ3.1
unnamed: D11.1, R28.7
unnamed: D12.1, R29.7
unnamed: D9.C, R29.4
unnamed: D12.3, R29.6
unnamed: D12.2, R29.8
unnamed: D11.3, R28.6
unnamed: D11.2, R28.8
unnamed: D2.1, R1.7
unnamed: R35.2, SJ4.3
unnamed: D3.1, R2.7
unnamed: R31.2, SJ4.1
unnamed: D15.1, R38.7
unnamed: D16.1, R39.7
unnamed: D13.C, R39.4
unnamed: D16.3, R39.6
unnamed: D16.2, R39.8
unnamed: D15.3, R38.6
unnamed: D15.2, R38.8
unnamed: R45.2, SJ5.3
unnamed: R41.2, SJ5.1
unnamed: D19.1, R48.7
unnamed: D20.1, R49.7
unnamed: D17.C, R49.4
unnamed: D20.3, R49.6
unnamed: D20.2, R49.8
unnamed: D19.3, R48.6
unnamed: D19.2, R48.8
unnamed: R55.2, SJ6.3
unnamed: R51.2, SJ6.1
unnamed: D23.1, R58.7
unnamed: D24.1, R59.7
unnamed: D21.C, R59.4
unnamed: D24.3, R59.6
unnamed: D24.2, R59.8
unnamed: D23.3, R58.6
unnamed: D23.2, R58.8
unnamed: R65.2, SJ7.3
unnamed: R61.2, SJ7.1
unnamed: D27.1, R68.7
unnamed: D28.1, R69.7
unnamed: D25.C, R69.4
unnamed: D28.3, R69.6
unnamed: D28.2, R69.8
unnamed: D27.3, R68.6
unnamed: D27.2, R68.8
unnamed: R75.2, SJ8.3
unnamed: R71.2, SJ8.1
unnamed: D31.1, R78.7
unnamed: D32.1, R79.7
unnamed: D29.C, R79.4
unnamed: D32.3, R79.6
unnamed: D32.2, R79.8
unnamed: D31.3, R78.6
unnamed: D31.2, R78.8
unnamed: R85.2, SJ9.3
unnamed: R81.2, SJ9.1
unnamed: D35.1, R88.7
unnamed: D36.1, R89.7
unnamed: D33.C, R89.4
unnamed: D36.3, R89.6
unnamed: D36.2, R89.8
unnamed: D35.3, R88.6
unnamed: D35.2, R88.8
unnamed: R95.2, SJ10.3
unnamed: R91.2, SJ10.1
unnamed: D39.1, R98.7
unnamed: D40.1, R99.7
unnamed: D37.C, R99.4
unnamed: D40.3, R99.6
unnamed: D40.2, R99.8
unnamed: D39.3, R98.6
unnamed: D39.2, R98.8
unnamed: R105.2, SJ11.3
unnamed: R101.2, SJ11.1
unnamed: D43.1, R108.7
unnamed: D44.1, R109.7
unnamed: D41.C, R109.4
unnamed: D44.3, R109.6
unnamed: D44.2, R109.8
unnamed: D43.3, R108.6
unnamed: D43.2, R108.8
unnamed: R115.2, SJ12.3
unnamed: R111.2, SJ12.1
unnamed: D47.1, R118.7
unnamed: D48.1, R119.7
unnamed: D45.C, R119.4
unnamed: D48.3, R119.6
unnamed: D48.2, R119.8
unnamed: D47.3, R118.6
unnamed: D47.2, R118.8
unnamed: R125.2, SJ13.3
unnamed: R121.2, SJ13.1
unnamed: D51.1, R128.7
unnamed: D52.1, R129.7
unnamed: D49.C, R129.4
unnamed: D52.3, R129.6
unnamed: D52.2, R129.8
unnamed: D51.3, R128.6
unnamed: D51.2, R128.8
unnamed: R135.2, SJ14.3
unnamed: R131.2, SJ14.1
unnamed: D55.1, R138.7
unnamed: D56.1, R139.7
unnamed: D53.C, R139.4
unnamed: D56.3, R139.6
unnamed: D56.2, R139.8
unnamed: D55.3, R138.6
unnamed: D55.2, R138.8
unnamed: R145.2, SJ15.3
unnamed: R141.2, SJ15.1
unnamed: D59.1, R148.7
unnamed: D60.1, R149.7
unnamed: D57.C, R149.4
unnamed: D60.3, R149.6
unnamed: D60.2, R149.8
unnamed: D59.3, R148.6
unnamed: D59.2, R148.8
unnamed: R155.2, SJ16.3
unnamed: R151.2, SJ16.1
unnamed: D63.1, R158.7
unnamed: D64.1, R159.7
unnamed: D61.C, R159.4
unnamed: D64.3, R159.6
unnamed: D64.2, R159.8
unnamed: D63.3, R158.6
unnamed: D63.2, R158.8
unnamed: R165.2, SJ17.3
unnamed: R161.2, SJ17.1
unnamed: D67.1, R168.7
unnamed: D68.1, R169.7
unnamed: D65.C, R169.4
unnamed: D68.3, R169.6
unnamed: D68.2, R169.8
unnamed: D67.3, R168.6
unnamed: D67.2, R168.8
unnamed: R175.2, SJ18.3
unnamed: R171.2, SJ18.1
unnamed: D71.1, R178.7
unnamed: D72.1, R179.7
unnamed: D69.C, R179.4
unnamed: D72.3, R179.6
unnamed: D72.2, R179.8
unnamed: D71.3, R178.6
unnamed: D71.2, R178.8
unnamed: R185.2, SJ19.3
unnamed: R181.2, SJ19.1
unnamed: D75.1, R188.7
unnamed: D76.1, R189.7
unnamed: D73.C, R189.4
unnamed: D76.3, R189.6
unnamed: D76.2, R189.8
unnamed: D75.3, R188.6
unnamed: D75.2, R188.8
unnamed: R195.2, SJ20.3
unnamed: R191.2, SJ20.1
unnamed: D79.1, R198.7
unnamed: D80.1, R199.7
unnamed: D77.C, R199.4
unnamed: D80.3, R199.6
unnamed: D80.2, R199.8
unnamed: D79.3, R198.6
unnamed: D79.2, R198.8
unnamed: R205.2, SJ21.3
unnamed: R201.2, SJ21.1
unnamed: D83.1, R208.7
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
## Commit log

2015-02-06 Fork of https://github.com/MightyQ/Qduino-Mini with irrelevant files and versions removed
2015-02-06 Converted simple things to SparkFun styles
2015-02-18 Added pullup resistors, added alrt interrupt trace, added PROD_ID to each part, swapped out SFE already used parts, etc
2015-02-18 Added missing prod_id for switch
2015-02-24 Dropped resonator to 8MHz for battery use & fixed some silk
2015-02-24 Pushed silk around
2015-02-24 Added label to SJ1
2015-02-25 Fixed library caused(?) inconsistencies
2015-02-26 Added logos to sch, massaged silk & a trace
2015-02-26 Added vias to USB connector pads to improve mechanical strength (from what I hear)
2015-04-07 Complete rework
2015-04-07 Fixed PROD_ID on caps again
2015-04-08 Renamed a few parts and removed gnd traces under gnd pours
2015-04-08 Converted more parts to parts SFE uses
2015-04-08 Fixed a little silk
2015-04-14 Labled LED flags to the colors ther were hooked up to and replaced the RGB LEDs with the footprint for the new part. STUFF IS BROKEN.
2015-04-24 Quin reworked the layout to fit the correct footprints for the LEDs he bought
2015-04-24 Added more ground pour, removed acid traps, cosmetic tweaks
2015-04-25 Shifted things, added vias to pads & added more silk.
2015-04-25 internally connected solder jumper, moved traces around new vias on USB
2015-04-25 moved some traces around to make them shorter
2015-04-27 Added note to follow USB spec for USB port
2015-04-27 Removed stray negative label from battery connector
2015-04-27 Removed 4th for-the-user LED, D5 & its current limit resistor
2015-05-08 Added first test of IDE 1.6.4 board support
2015-05-08 updated json file with new URL
2015-05-09 Update package_qtechknow_index.json
    fixes
2015-05-09 Update package_qtechknow_index.json
    Changed tarball hosting to something I control so I could get the right filename.
2015-05-09 Update package_qtechknow_index.json
    Updated Boards menu divider
2015-05-11 Fixed(?) platform name
2015-05-11 Updated CS file
2015-05-12 bumped BOD level from 2.0V to 2.4V
2015-05-12 updated checksum
2015-05-18 Added IC prefix to a part attribute & updated tarball URL to final destination (invalid until repo is public)
2015-05-28 Nudged a little silk and removed battery polarity from the bottom
2015-05-28 Removed castellated vias
2015-05-28 Bumped version to 10
2015-05-29 Improved ground path from LiPo to GND pin nearby. Increased width of LiPo & Vbus by 25-50%
2015-05-29 Fixed issues
2015-05-29 Switched LEDs to those in the live library vs testing
2015-06-01 Moved Arduino board manager code to Software dir
2015-06-01 created panel v10
2015-06-02 Updated PROD_ID for Vreg to new part
2015-06-02 Added 10KΩ pull-up to reset line
2015-06-03 deleted old panel
2015-06-03 Nudged traces and changed orientation of resistor
    Nudged traces and moved 10K resistor for better trace continuity and
    silk arrangement
2015-06-03 Cleaned up silk near recent changes
2015-06-03 Fixed USB silk on bottom
2015-06-05 created panel v10 again
2015-06-19 RXLED & TXLED were swapped. Noted errata.
2015-07-13 Update boards.txt
    Fixed VIDs
2015-07-13 added drivers to package
2015-07-17 Added notes to schematic & updated board manager files
2015-07-17 Removed redundant files. Use the copy in the tarball
2015-07-20 added Quin's library & examples
2015-07-21 Minor tweaks
2015-07-21 added missing files
2015-08-13 Fixed stray PID
2015-08-13 Defined another string in inf for Windows
2015-08-18 Updated Windows driver setup info file to newer format
2015-08-24 Added version # to tarball to force a unique download and prevent CRC errors
2015-08-24 Updated reference to tarball
2015-08-25 Signed Windows driver
2015-09-03 Fixed MISO D# & powered USB LEDs directly from USB
2015-09-03 Reduced isolate to dramatically increase ground pour
2015-09-04 Incremented version number and panelized
2015-09-09 Updated to new DFN-8 pacakge for fuel gauge IC & version++
2015-09-09 Moved resistor arrays 25mil further away from LEDs for rework
2015-09-11 Moved battery silk
2015-09-11 Reduced DFN-8 center pad paste by 40%
2015-09-11 Reduced tstop to center of IPC recommended range (135 µm) rather than toward the wide end
2015-09-23 Kickstarter design with production tweaks. Keeping the flicker for software compatibility reasons
2015-09-23 Incremented version number
2015-09-23 Added tRestrict to prevent copper from going under resonator footprint's tStop
2015-10-22 Removed redundant gnd path on USB
2015-10-28 created panel v14
2016-01-05 Updated software version to current version in Kickstarter repo
2016-01-06 Updated URL for archive
2016-01-06 Added gitattributes file
2016-01-07 Updated image to current version
2016-01-07 Updated pin map with new definitions
2016-01-08 Removed software. It's now maintained in our Arduino_Boards repo
2016-02-10 Expanded on license file
2016-02-11 Update LICENSE.md
    Quin wrote the majority of the code, changing our default license to give him the credit.
